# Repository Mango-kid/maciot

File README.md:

## Mac-IOT Board

Please check out the [Wiki](https://github.com/Mango-kid/maciot/wiki) for more information on the board design, programming and software setup.  

## Specifications
* bluetooth and(or) wifi capable
* programmable over USB with simple programming IDE
* 4 on board LEDs
* 4 on board switches
* some interactive sensors
* powered by USB or other battery supply
* can use existing Arduino sheild eco-system
***
## License
This project is licensed under the GPLv3 license.

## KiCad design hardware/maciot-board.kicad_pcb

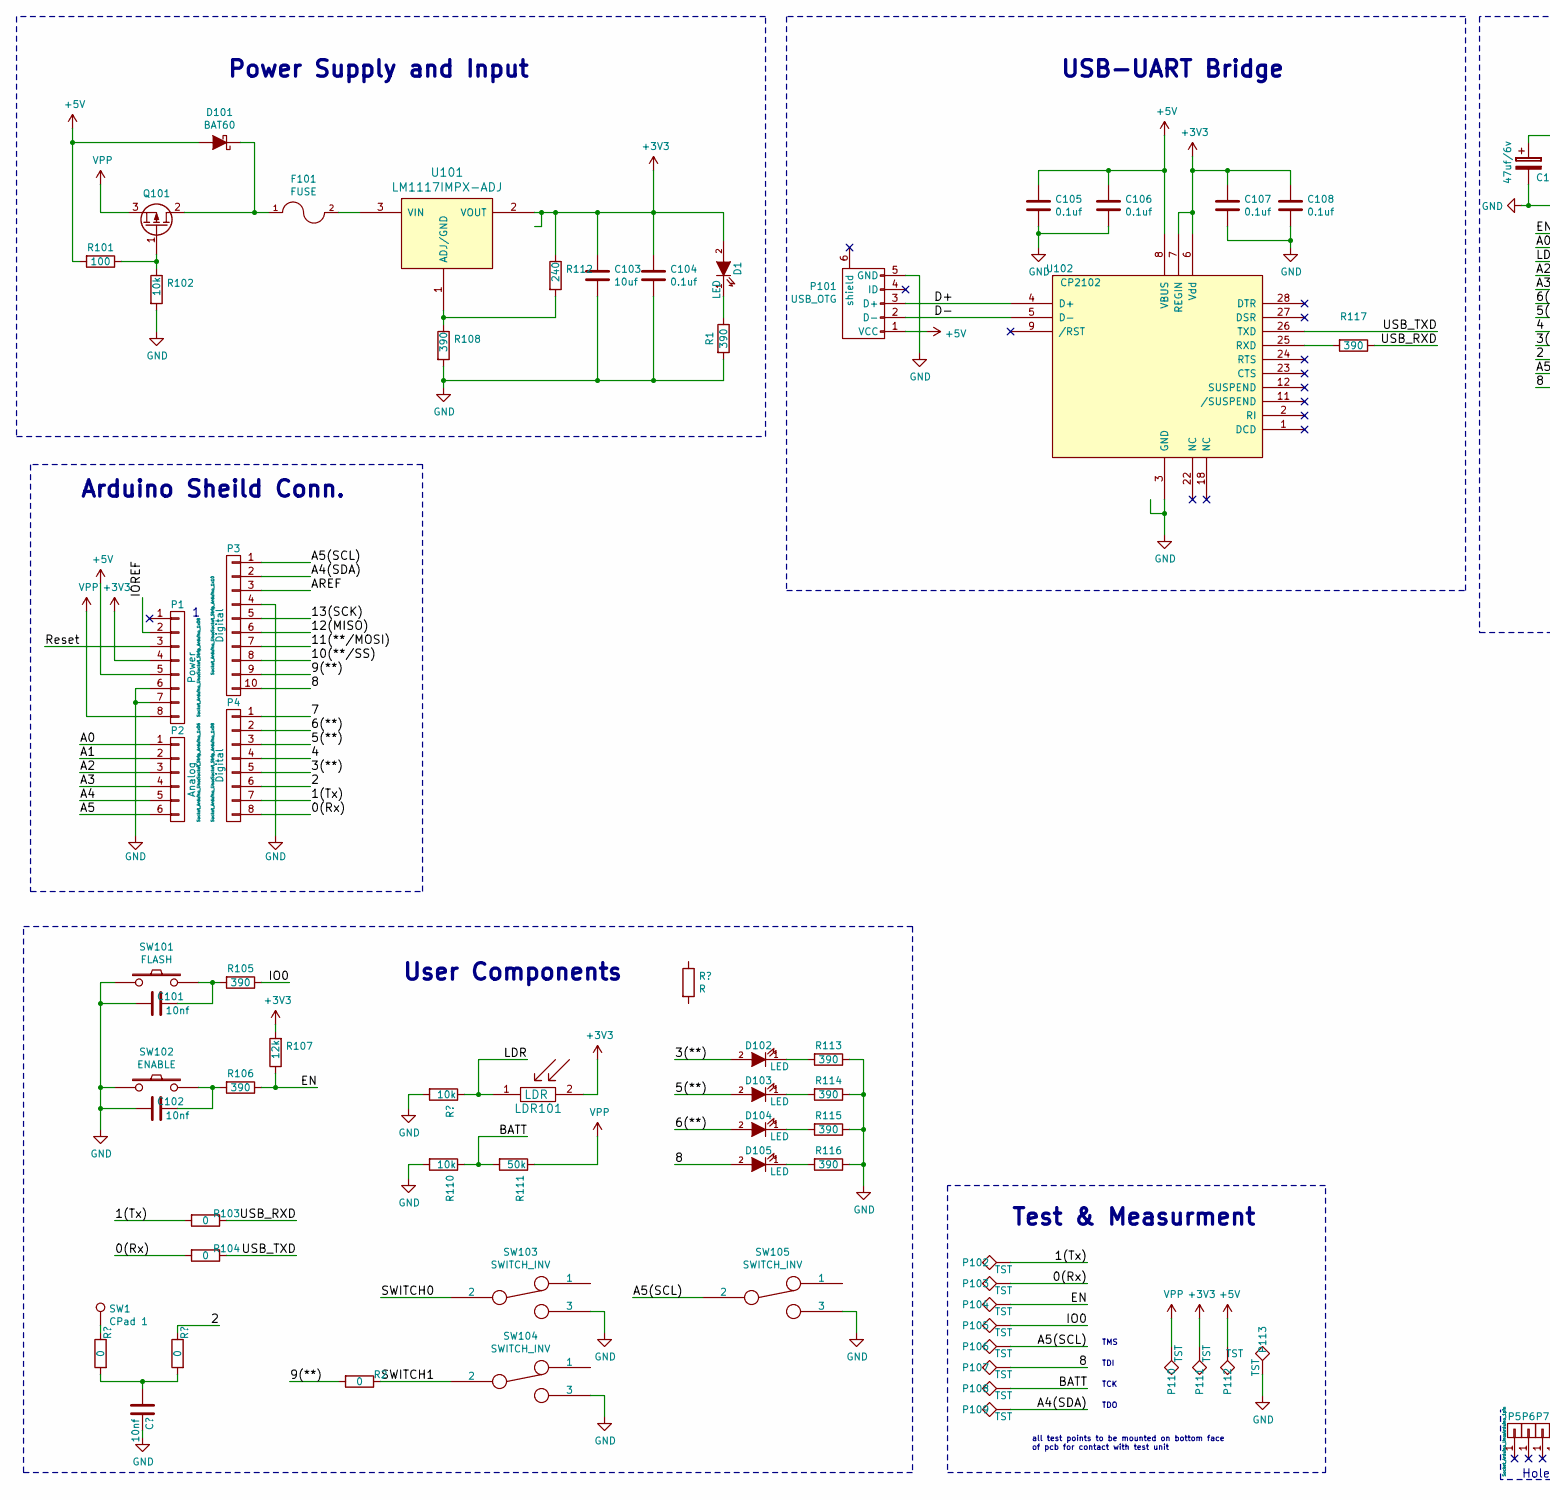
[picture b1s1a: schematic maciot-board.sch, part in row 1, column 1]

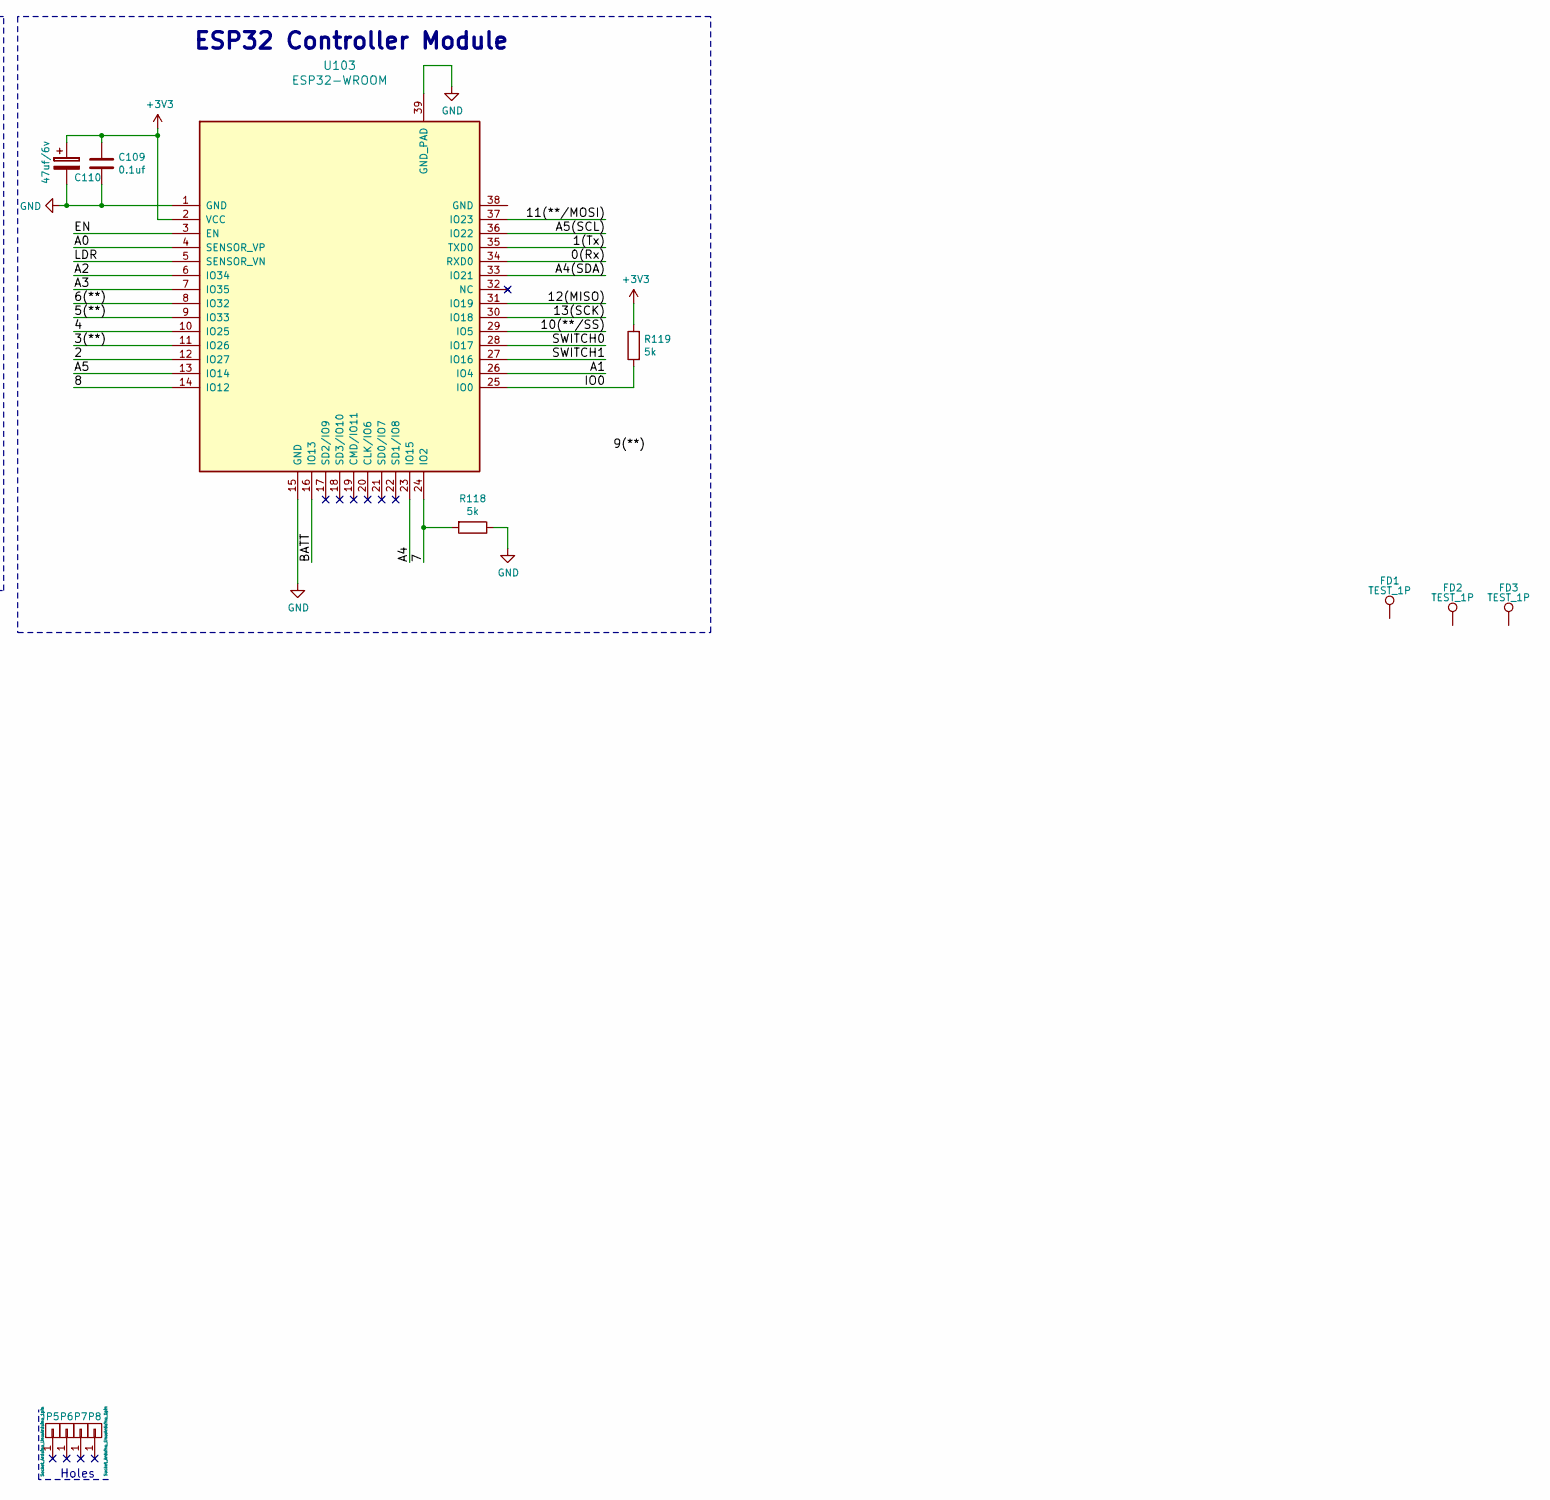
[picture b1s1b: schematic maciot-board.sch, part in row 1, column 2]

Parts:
C101, C102: 10nf; c_0805; mouser# 81-GRM40X103K50D
C103: 10uf; c_1210; mouser# 77-VJ1210V106ZXJTBC
C104: 0.1uf; c_0805; mouser# 81-GCM21BR71H104KA37
C105: 0.1uf; c_0805; mouser# 81-GCM21BR71H104KA38
C106: 0.1uf; c_0805; mouser# 81-GCM21BR71H104KA39
C107: 0.1uf; c_0805; mouser# 81-GCM21BR71H104KA40
C108: 0.1uf; c_0805; mouser# 81-GCM21BR71H104KA41
C109: 0.1uf; c_0805; mouser# 81-GCM21BR71H104KA42
C110: 47uf/6v; c_1206; mouser# TAJA476K006SNJV
D1, D102, D103, D104, D105: LED; Led_0805; mouser# 604-AP2012YD
D101: BAT60; sod323; mouser# 726-BAT60AE6327HTSA1
F101: FUSE; r_1210; mouser# 652-MF-USMF050-2
FD1, FD2, FD3: TEST_1P; Fiducial_1mm_Dia_2.54mm_Outer_CopperTop
LDR101: LDR; digi# PDV-P8103-ND
P1: Power; Socket_Strip_Arduino_1x08; mouser# 474-PRT-09279
P2: Analog; Socket_Strip_Arduino_1x06; mouser# 474-PRT-09280
P3: Digital; Socket_Strip_Arduino_1x10; mouser# 474-PRT-11376
P4: Digital; Socket_Strip_Arduino_1x08; mouser# 474-PRT-09279
P5, P6, P7, P8: CONN_01X01; Arduino_1pin
P101: USB_OTG; conn_usb_B_micro_smd; mouser# 10118192-0001LF
P102, P103, P104, P105, P106, P107, P108, P109, P110, P111, P112, P113: TST; Measurement_Point_Round-SMD-Pad_Small
Q101: Q_PMOS_GDS; sot23; mouser# 771-PMV48XP215
R1, R105, R106, R108, R113, R114, R115, R116, R117: 390; r_0805; mouser# ERJ-6GEYJ391V
R2, R103, R104: 0; r_0805; mouser# ERJ-6GEY0R00V
R101: 100; r_0805; mouser# ERJ-6ENF1000V
R102, R110: 10k; r_0805; mouser# ERJ-6GEYJ103V
R107: 12k; r_0805; mouser# ERJ-6GEYJ123V
R111: 50k; r_0805; mouser# ERJ-6ENF4992V
R112: 240; r_0805; mouser# ERJ-6GEYJ241V
R118, R119: 5k; r_0805; mouser# ERJ-6ENF4991V
SW1: CPad 1
SW101: FLASH; PCB_PUSH; mouser# 506-FSM4JAH
SW102: ENABLE; PCB_PUSH; mouser# 506-FSM4JAH
SW103, SW104, SW105: SWITCH_INV; OS102011MS2QN1 Slide Switch; mouser# 611-OS102011MS2QN1
U101: LM1117IMPX-ADJ; sot223; mouser# 926-M1117IMPXADJNOPB
U102: CP2102; QFN-28-1EP_5x5mm_Pitch0.5mm; mouser# 634-CP2102-GM
U103: ESP32-WROOM

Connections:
+3V3: C103.1, C104.1, C107.1, C108.1, C109.1, C110.1, D1.2 (A), LDR101.2, P1.4, P111.1, R107.2, R112.1, R119.2, U101.2 (VOUT), U101.4 (VOUT), U102.6 (Vdd), U102.7 (REGIN), U103.2 (VCC)
+5V: C105.1, C106.1, D101.2 (A), P1.5, P101.1 (VCC), P112.1, R101.2, U102.8 (VBUS)
/0(Rx): P4.8, P103.1, R104.2, U103.34 (RXD0)
/1(Tx): P4.7, P102.1, R103.2, U103.35 (TXD0)
/2: P4.6, U103.12 (IO27); also elsewhere on the board
/3(**): D102.2 (A), P4.5, U103.11 (IO26)
/4: P4.4, U103.10 (IO25)
/5(**): D103.2 (A), P4.3, U103.9 (IO33)
/6(**): D104.2 (A), P4.2, U103.8 (IO32)
/7: P4.1, R118.2, U103.24 (IO2)
/8: D105.2 (A), P3.10, P107.1, U103.14 (IO12)
/9(**): P3.9, R2.2
/10(**/SS): P3.8, U103.29 (IO5)
/11(**/MOSI): P3.7, U103.37 (IO23)
/12(MISO): P3.6, U103.31 (IO19)
/13(SCK): P3.5, U103.30 (IO18)
/A0: P2.1, U103.4 (SENSOR_VP)
/A1: P2.2, U103.26 (IO4)
/A2: P2.3, U103.6 (IO34)
/A3: P2.4, U103.7 (IO35)
/A4: P2.5, U103.23 (IO15)
/A4(SDA): P3.2, P109.1, U103.33 (IO21)
/A5: P2.6, U103.13 (IO14)
/A5(SCL): P3.1, P106.1, SW105.2, U103.36 (IO22)
/AREF: P3.3
/BATT: P108.1, R110.1, R111.2, U103.16 (IO13)
/D+: P101.3 (D+), U102.4 (D+)
/D-: P101.2 (D-), U102.5 (D-)
/EN: P104.1, R106.1, R107.1, U103.3 (EN)
/IO0: P105.1, R105.1, R119.1, U103.25 (IO0)
/IOREF: P1.2
/LDR: LDR101.1, U103.5 (SENSOR_VN); also elsewhere on the board
/Reset: P1.3
/SWITCH0: SW103.2, U103.28 (IO17)
/SWITCH1: R2.1, SW104.2, U103.27 (IO16)
/USB_RXD: R103.1, R117.1
/USB_TXD: R104.1, U102.26 (TXD)
GND: C101.2, C102.2, C103.2, C104.2, C105.2, C106.2, C107.2, C108.2, C109.2, C110.2, P1.6, P1.7, P3.4, P101.5 (GND), P113.1, R1.2, R102.2, R108.2, R110.2, R113.1, R114.1, R115.1, R116.1, R118.1, SW101.1, SW102.1, SW103.3, SW104.3, SW105.3, U102.3 (GND), U102.29 (GND), U103.1 (GND), U103.15 (GND), U103.39 (GND_PAD); also elsewhere on the board
unnamed: C101.1, R105.2, SW101.2
unnamed: C102.1, R106.2, SW102.2
unnamed: D1.1 (K), R1.1
unnamed: D101.1 (K), F101.1, Q101.2 (D)
unnamed: D102.1 (K), R113.2
unnamed: D103.1 (K), R114.2
unnamed: D104.1 (K), R115.2
unnamed: D105.1 (K), R116.2
unnamed: F101.2, U101.3 (VIN)
unnamed: Q101.1 (G), R101.1, R102.1
unnamed: R108.1, R112.2, U101.1 (ADJ/GND)
unnamed: R117.2, U102.25 (RXD)
unnamed: U102.10 (NC), U102.13 (NC), U102.14 (NC), U102.15 (NC), U102.16 (NC), U102.17 (NC), U102.19 (NC), U102.20 (NC), U102.21 (NC), U102.22 (NC)
VPP: P1.8, P110.1, Q101.3 (S), R111.1

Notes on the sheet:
Holes
Power Supply and Input
USB-UART Bridge
TMS
TDI
TCK
TDO
Test & Measurment
all test points to be mounted on bottom face of pcb for contact with test unit
ESP32 Controller Module
User Components
Arduino Sheild Conn.

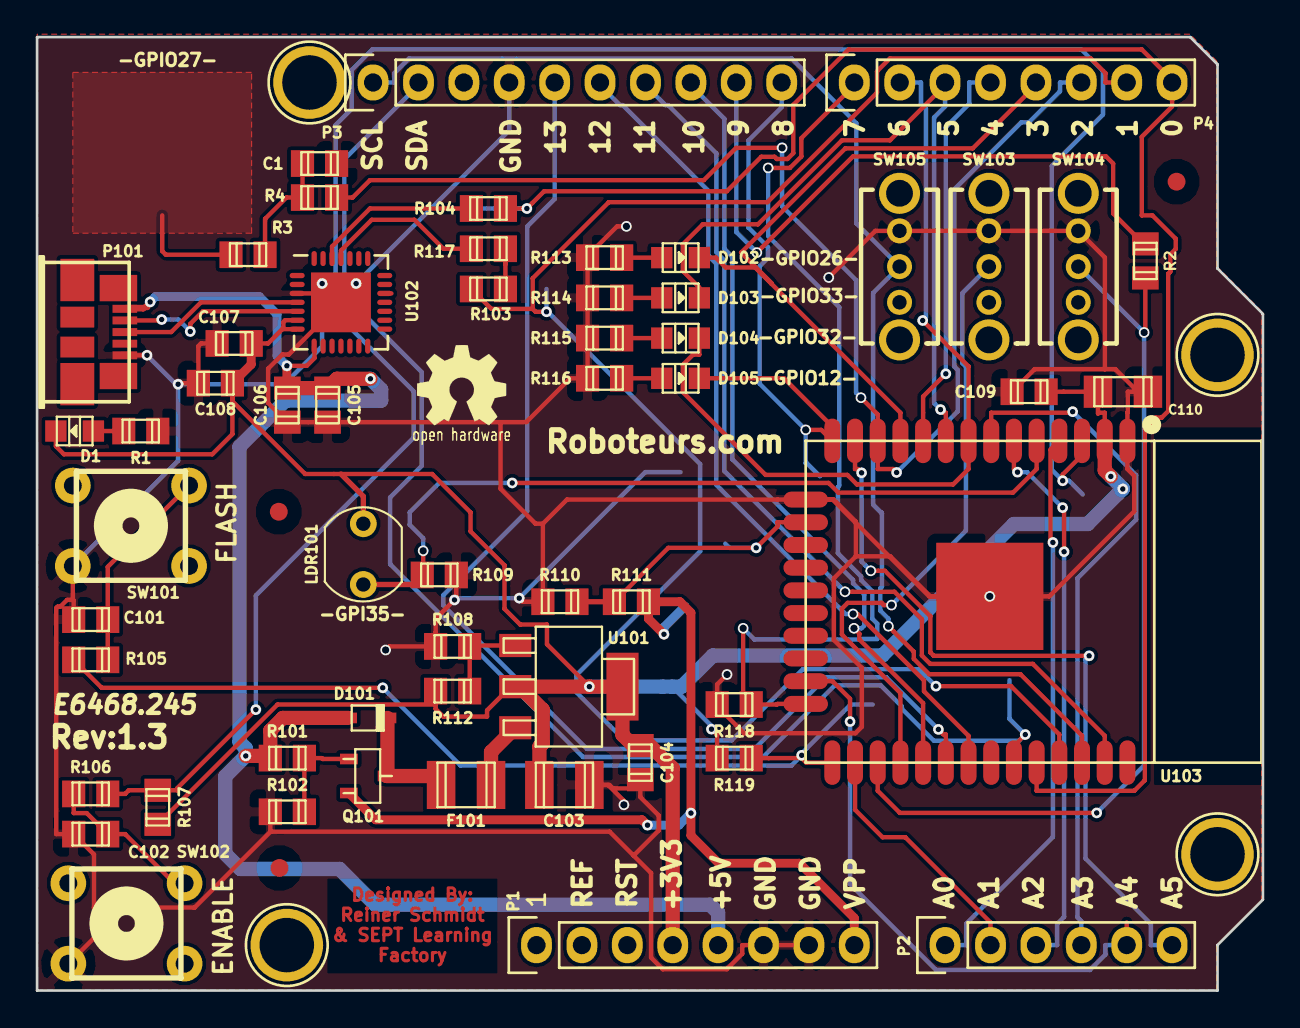
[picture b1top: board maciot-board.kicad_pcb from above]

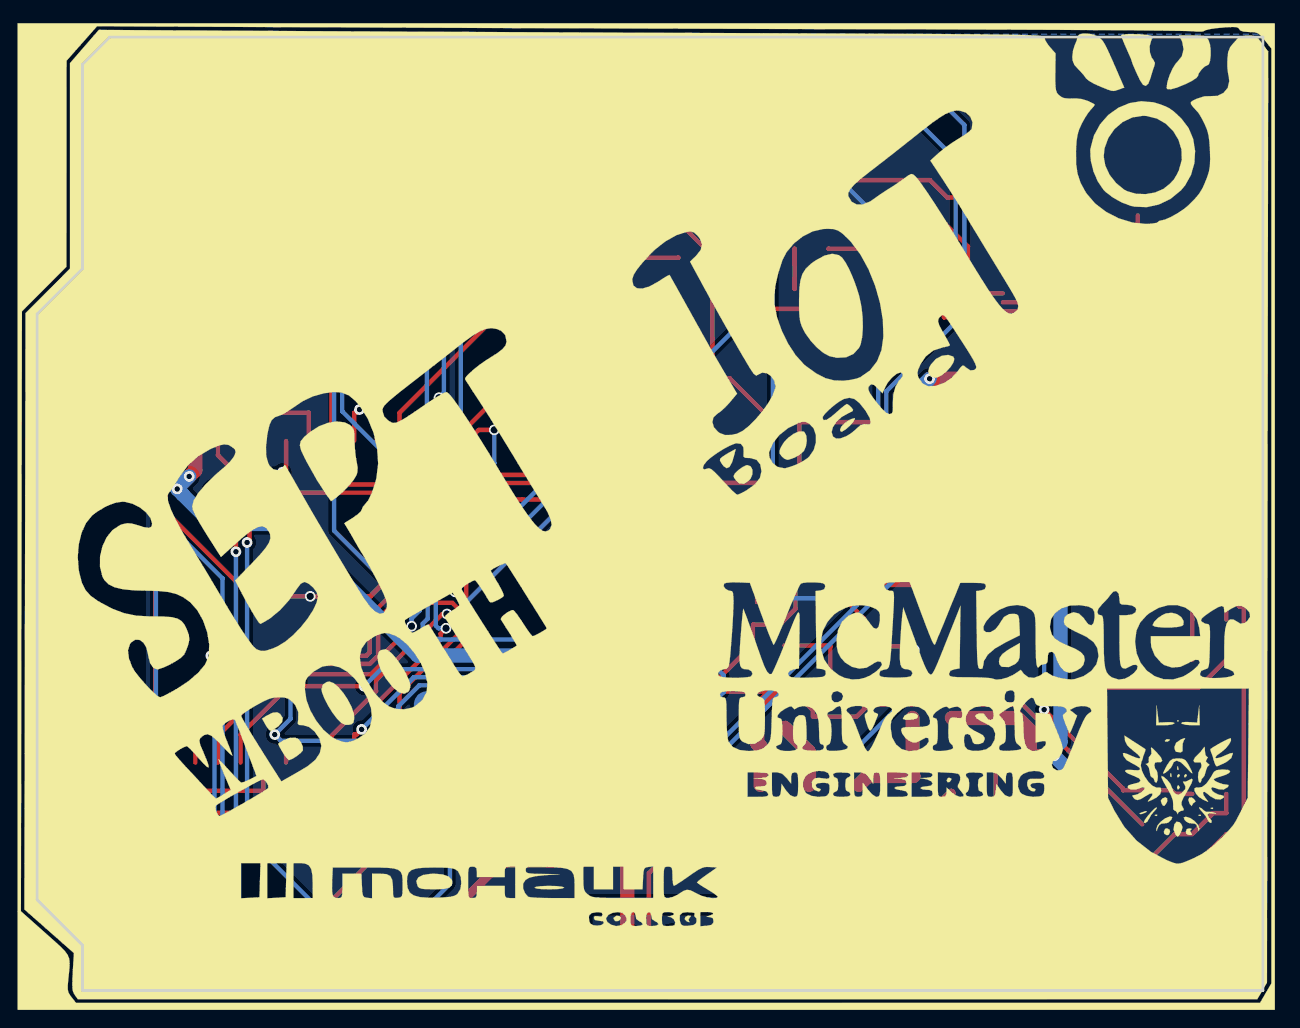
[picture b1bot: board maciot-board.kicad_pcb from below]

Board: 2 copper layers, 68.6 x 53.3 mm, 75 parts (12 on the bottom side), 50 nets.

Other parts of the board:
C1: 10nf; c_0805
R3, R4: 0; r_0805
R109: 100k; r_0805

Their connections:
/2: R4.2; also elsewhere on the board
/LDR: R109.1; also elsewhere on the board
GND: C1.1, R109.2; also elsewhere on the board
unnamed: C1.2, R3.1, R4.1

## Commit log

2017-06-12 inital commit
2017-06-12 updated board name
2017-06-12 iniital commit
2017-06-12 simple edits
2017-09-18 simple updates
2018-05-28 added cap pad
